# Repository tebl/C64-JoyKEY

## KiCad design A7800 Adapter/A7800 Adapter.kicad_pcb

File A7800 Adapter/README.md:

# JoyKEY (Atari 7800 Adapter)
**UNTESTED**

In the age of the Commmodore 64, Atari decided that it was a good idea to put together a console without audio quality that would only rise to the level of competing with the almighty ZX Spectrum. Then they launched them with horrible controllers that fell part on the way home from the store. Here in Europe, we also got treated to a gamepad-like controller that can only be described as an implement created by someone who only have had the concept just barely described to them over the phone - yet, we still got the feeling that they hated gamers.

Enough about all that, I actually have more than one of the consoles - somehow I sort of like playing on them, I just can't use any of their controllers. I've previously made an adapter so that I can use Sega Mega Drive controllers with the console, but since I've built the *C64 JoyKEY* I wanted to use it on that as well (which is the reason for this adapter).

# BOM
The parts listed are the ones I've used when building an Atari 7800 controller adapter for the *C64 JoyKEY*, part listed in parenthesis are considered optional (meaning you could build a more limited version of it). 

| Reference     | Item                                      | Count |
| ------------- | ----------------------------------------- | ----- |
| PCB           | Fabricate using Gerber files ([order]())  |    (1)|
| J1 *          | 2x5 pin straight header pins or 2x5 IDC   |     1 |
| J2 **         | DE-9 Female straight connector            |     1 |
| JP1,JP2 ***   | 3-pin breakable header pins (w/jumpers    |    (2)|

*) Breakable dual row pin headers can be used here, but I find it is nicer to use a 2x5 pin connector here instead. The cable needed is a 2x5 pin IDC cable (usually listed as *AVR* or *JTAG* cable) with sufficient length.

**) These are the blue kind with straight pins, it will include a few metal bits on it - remove those and you'll be left with the mostly blue part needed. Bend the pins slightly and match up with PCB, solder before it has a chance to fall off.

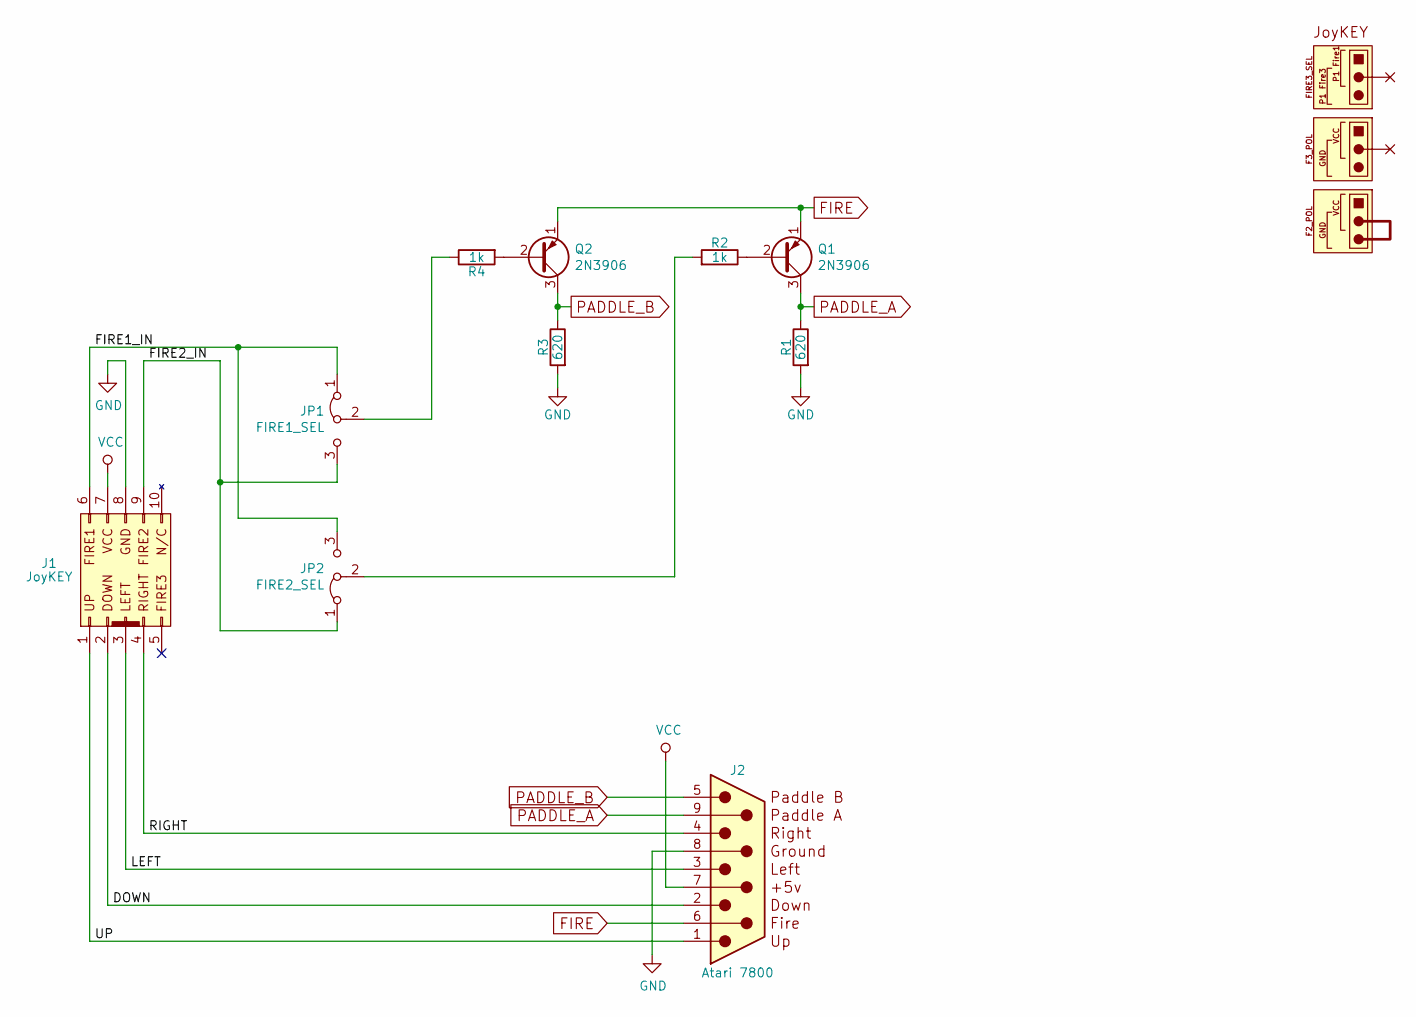
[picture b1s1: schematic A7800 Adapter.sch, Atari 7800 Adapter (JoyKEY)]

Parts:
J1: JoyKEY; IDC_Joystick
J2: Atari 7800; DSUB-9_Female_Edge
JP1: FIRE1_SEL; Pin_Header_Straight_1x03_Pitch2.54mm
JP2: FIRE2_SEL; Pin_Header_Straight_1x03_Pitch2.54mm
Q1, Q2: 2N3906; TO-92_Inline_Wide
R1, R3: 620; R_Axial_DIN0207_L6.3mm_D2.5mm_P10.16mm_Horizontal
R2, R4: 1k; R_Axial_DIN0207_L6.3mm_D2.5mm_P10.16mm_Horizontal

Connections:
/DOWN: J1.2, J2.2
/FIRE1_IN: J1.6, JP1.1 (A), JP2.3 (B)
/FIRE2_IN: J1.9, JP1.3 (B), JP2.1 (A)
/LEFT: J1.3, J2.3
/RIGHT: J1.4, J2.4
/UP: J1.1, J2.1
FIRE: J2.6, Q1.1 (E), Q2.1 (E)
GND: J1.8, J2.8 (GND), R1.2, R3.2
unnamed: JP1.2 (C), R4.1
unnamed: JP2.2 (C), R2.2
unnamed: Q1.2 (B), R2.1
unnamed: Q2.2 (B), R4.2
PADDLE_A: J2.9, Q1.3 (C), R1.1
PADDLE_B: J2.5, Q2.3 (C), R3.1
VCC: J1.7, J2.7 (VCC)

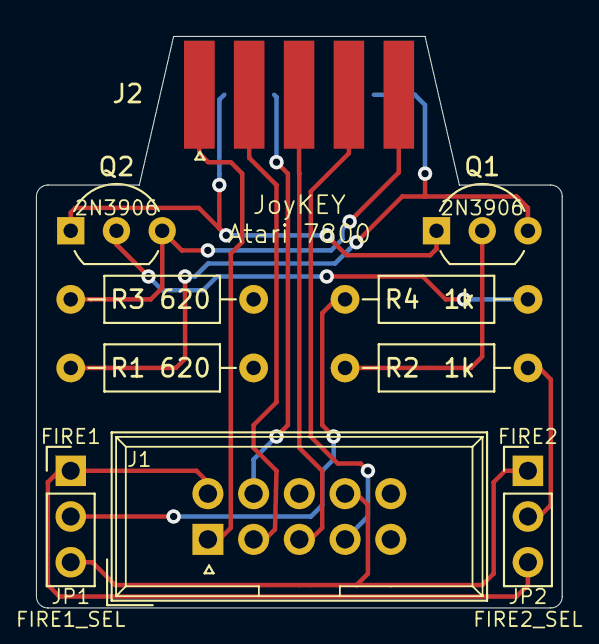
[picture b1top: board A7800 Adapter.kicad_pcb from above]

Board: 2 copper layers, 29.2 x 31.8 mm, 10 parts (0 on the bottom side), 15 nets.

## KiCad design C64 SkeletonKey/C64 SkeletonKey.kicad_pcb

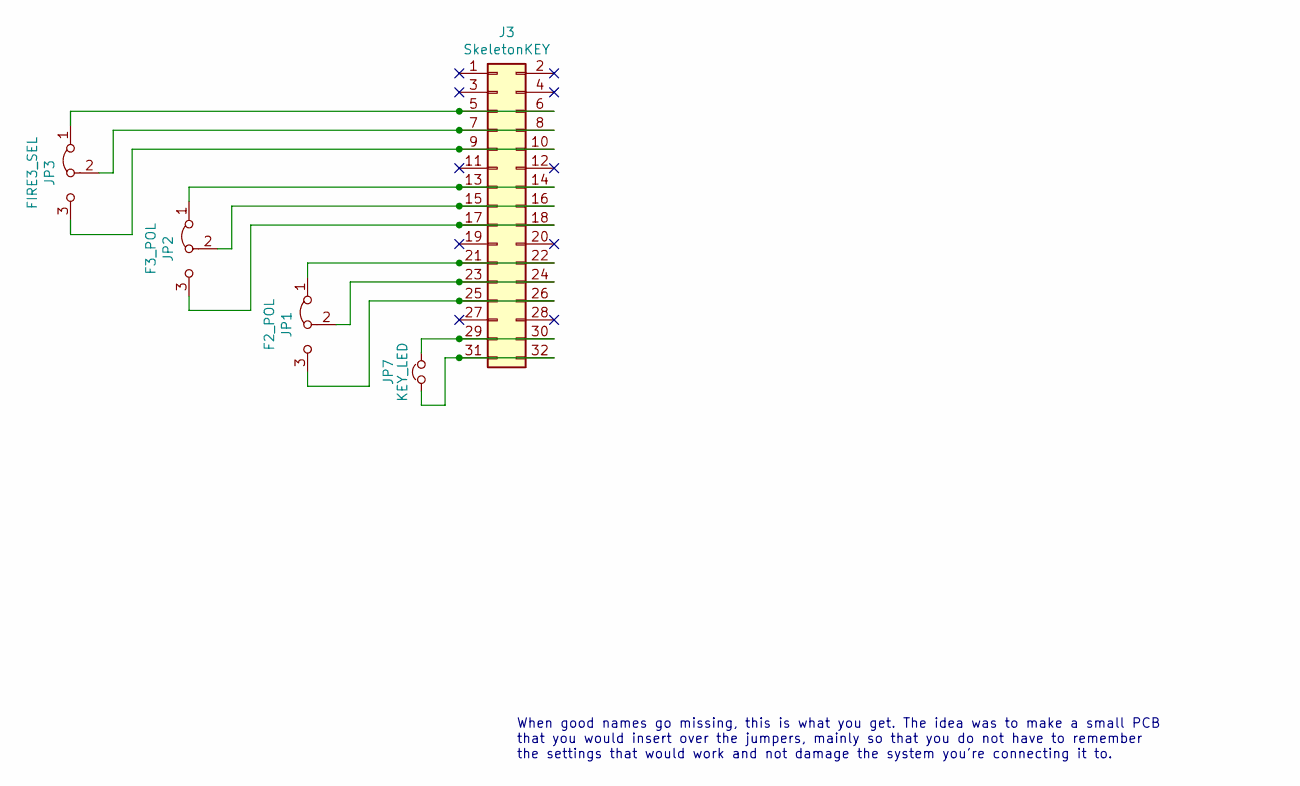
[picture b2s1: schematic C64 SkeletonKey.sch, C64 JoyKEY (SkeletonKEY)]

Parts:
J3: SkeletonKEY; PinHeader_2x16_P2.54mm_Vertical
JP1: F2_POL; select_r
JP2: F3_POL; select_r
JP3: FIRE3_SEL; select_r
JP7: KEY_LED; bridge_r

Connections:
unnamed: J3.5, J3.6, JP3.1 (A)
unnamed: J3.7, J3.8, JP3.2 (C)
unnamed: J3.9, J3.10, JP3.3 (B)
unnamed: J3.13, J3.14, JP2.1 (A)
unnamed: J3.15, J3.16, JP2.2 (C)
unnamed: J3.17, J3.18, JP2.3 (B)
unnamed: J3.21, J3.22, JP1.1 (A)
unnamed: J3.23, J3.24, JP1.2 (C)
unnamed: J3.25, J3.26, JP1.3 (B)
unnamed: J3.29, J3.30, JP7.1
unnamed: J3.31, J3.32, JP7.2

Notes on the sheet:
When good names go missing, this is what you get. The idea was to make a small PCB that you would insert over the jumpers, mainly so that you do not have to remember the settings that would work and not damage the system you're connecting it to.

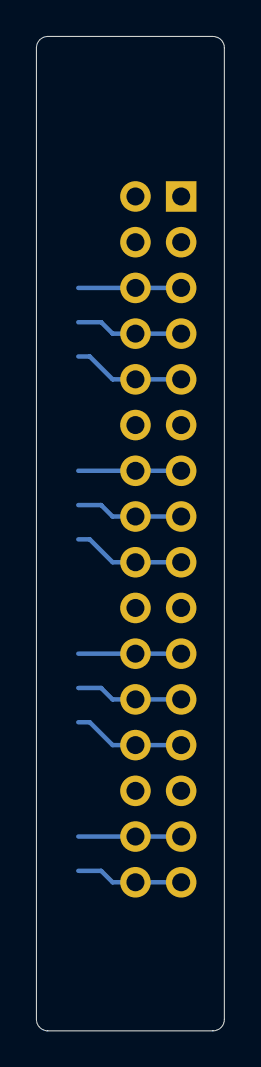
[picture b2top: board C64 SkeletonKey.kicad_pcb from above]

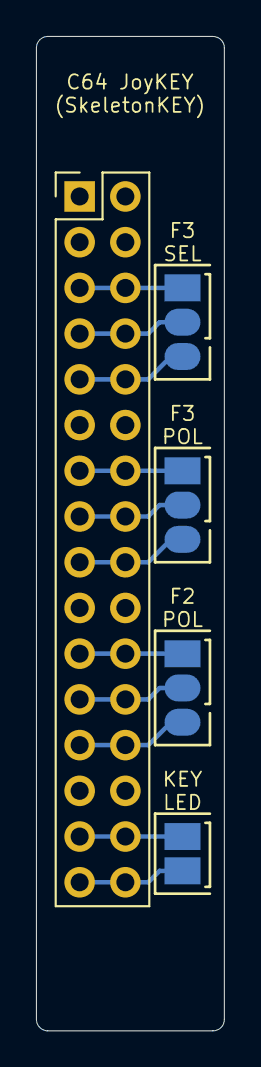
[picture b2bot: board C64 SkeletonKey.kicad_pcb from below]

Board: 2 copper layers, 10.4 x 55.2 mm, 5 parts (5 on the bottom side), 11 nets.

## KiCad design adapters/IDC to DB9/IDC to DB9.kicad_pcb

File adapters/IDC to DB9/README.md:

# IDC to DB9

An adapter that isn't actually an adapter might seem a bit strange at first look, but I promise that there's a use-case for it somewhere. One of them is that a few systems computers have recessed controller ports, the Commodore Amiga 600 is a rather common example of this. What that means in a slightly lesser amount of words, not by much, is that most DB9 connectors won't fit on these systems without using a hacksaw. That's why I created this small adapter, that is just a straight plug from 2x5 IDC to DB9. Another reason is that this way you can actually build the whole system without actually soldering wires onto a connector.

Given the rather generic use of this module compared to the others, I can't say anything about said systems ability to power a C64 JoyKEY with backlights and the whole package - I've added a power jumper so that we can stop the module from drawing power from the system (short **VCC_EN** if you know what you're doing).

# BOM
The parts listed are the ones I've used when building a Sinclair adapter for use with the *C64 JoyKEY*, part listed in parenthesis are considered optional (meaning you could build a more limited version of it). 

| Reference     | Item                                      | Count | Order   |
| ------------- | ----------------------------------------- | ----- | ------- |
| PCB           | Fabricate using Gerber files              |    (1)| [PCBway](https://www.pcbway.com/project/shareproject/C64_JoyKEY__IDC_to_DB9_.html)
| J1 *          | 2x5 pin straight header pins or 2x5 IDC   |     1 |
| J2 **         | DE-9 Female straight connector            |     1 |

*) Breakable dual row pin headers can be used here, but I find it is nicer to use a 2x5 pin connector here instead. The cable needed is a 2x5 pin IDC cable (usually listed as *AVR* or *JTAG* cable) with sufficient length.

**) These are the blue kind with straight pins, it will include a few metal bits on it - remove those and you'll be left with the mostly blue part needed. Bend the pins slightly and match up with PCB, solder before it has a chance to fall off.

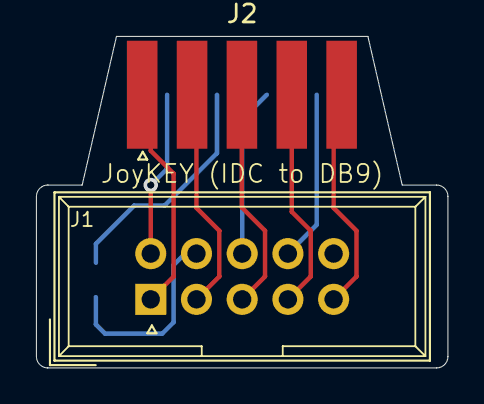
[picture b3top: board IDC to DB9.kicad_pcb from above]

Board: 2 copper layers, 22.9 x 18.4 mm, 3 parts (1 on the bottom side), 10 nets.

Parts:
J1: JoyKEY; IDC_Joystick
J2: DB9; DSUB-9_Female_Edge
JP1: PWR; bridge

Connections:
/DOWN: J1.2, J2.2
/FIRE1: J1.6, J2.6
/FIRE2: J1.9, J2.9
/FIRE3: J1.5, J2.5
/LEFT: J1.3, J2.3
/RIGHT: J1.4, J2.4
/UP: J1.1, J2.1
GND: J1.8, J2.8
unnamed: J1.7, JP1.1
VCC: J2.7, JP1.2

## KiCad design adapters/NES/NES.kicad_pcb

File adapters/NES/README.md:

# JoyKEY (Nintendo Entertainment System)
The Nintendo Entertainment System, commonly known as just the *NES* came with a four button controller (*B*, *A*, *SELECT* and *START*). A picture of the completed adapter has been included below, including the jumper position that you need to use on the *C64 JoyKEY* device itself.  For the later revisions of the *C64 JoyKEY* you'll have a row of buttons on the bottom left of the device, these are ideal for using as the  *SELECT* and *START* - for earlier revisions you'd install a physical *START*-button on the adapter itself.

Making the adapter requires a cable with the right shape, Nintendo wanted these to be explicitly proprietary so you can't exactly order one from electronic parts vendors though obtaining one isn't exactly hard. The simplest way of obtaining the plug today is either cutting up cheap NES controller extension cable, alternatively you could just purchase one of the rather horrible cloned controllers and cut it off from that instead. Both of these options should be readily available from your favourite off-brand marketplace for all things "*Made in China*", AliExpress, Ebay, Wish and most similar sites.

With the cut-off cable in hand, the individual strands of the cable can then be soldered to the adapter PCB. The pins are numbered left to right, match up the individual strands to the pin numbering as shown in the [schematic](https://github.com/tebl/C64-JoyKEY/blob/main/documentation/schematic/adapters/NES.pdf). Ideally I'd like to just tell you where to connect them based on the colour, but with the cost of these things I wouldn't expect them to be identical across all of them - so just use your multimeter in order to identify what goes where on the connector.

# BOM
The parts listed are the ones I've used when building a Nintendo Entertainment System controller adapter for the *C64 JoyKEY*, part listed in parenthesis are considered optional (meaning you could build a more limited version of it).

| Reference     | Item                                      | Count | Order  |
| ------------- | ----------------------------------------- | ----- | ------ |
| PCB           | Fabricate using Gerber files              |     1 | [PCBWay](https://www.pcbway.com/project/shareproject/C64_JoyKEY_NES_adapter_74ada4a5.html)
| J1,J2 *       | 2x5 pin straight header pins or 2x5 IDC   |     2 |
| J3            | Male end of NES extension cable           |     1 |
| JP1           | 2-pin breakable header pins (w/jumpers)   |    (1)|
| R1-R8         | 1k ohm resistor                           |     9 | 
| SW1 **        | 6x6mm momentary tactile switch            |    (1)|
| U1            | CD4021BE (DIP-16)                         |     1 |

*) Breakable dual row pin headers can be used here, but I find it is nicer to use a 2x5 pin connector here instead. The cable needed is a 2x5 pin IDC cable (usually listed as *AVR* or *JTAG* cable) with sufficient length, these are used with all adapters.

**) This switch is only required using an earlier revision of the *C64 JoyKEY*, the three extra switches were added in revision E.

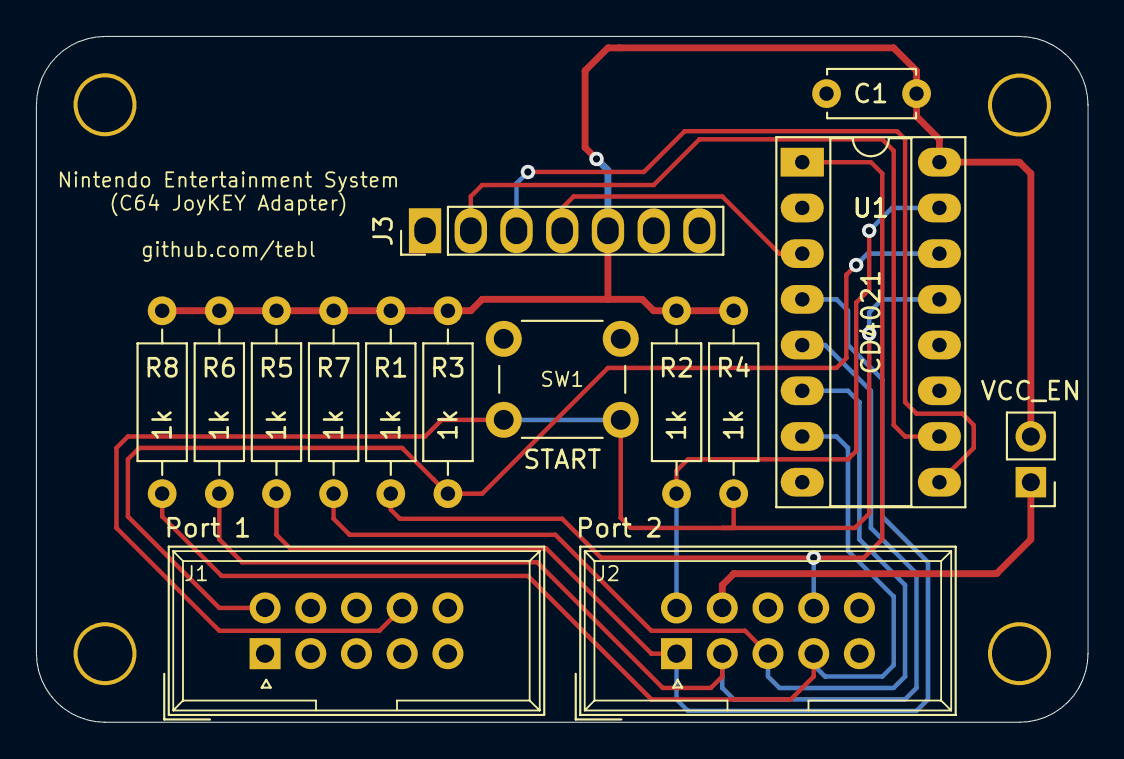
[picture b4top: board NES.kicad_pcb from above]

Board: 2 copper layers, 58.4 x 38.1 mm, 19 parts (0 on the bottom side), 14 nets.

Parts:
C1: 100nF; C_Disc_D4.7mm_W2.5mm_P5.00mm
J1: Port 1; IDC_Joystick
J2: Port 2; IDC_Joystick
J3: NES_Gamepad; NES_Output
JP1: VCC_EN; PinHeader_1x02_P2.54mm_Vertical
M1, M2, M3, M4: Mounting; M3_pin
R1, R2, R3, R4, R5, R6, R7, R8: 1k; R_Axial_DIN0207_L6.3mm_D2.5mm_P10.16mm_Horizontal
SW1: START; SW_PUSH_6mm
U1: CD4021; DIP-16_W7.62mm_Socket_LongPads

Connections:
/A: J2.9, R1.2, U1.1
/B: J2.6, R2.2, U1.15
/DOWN: J2.2, R6.2, U1.5
/LEFT: J2.3, R7.2, U1.6
/RIGHT: J2.4, R8.2, U1.7
/SELECT: J1.6, R3.2, U1.14
/START: J1.9, R4.2, SW1.2, U1.13
/UP: J2.1, R5.2, U1.4
CLK: J3.2, U1.10
DATA: J3.4, U1.3
GND: C1.2, J1.8, J2.8, J3.1, SW1.1, U1.8, U1.11
LATCH: J3.3, U1.9
unnamed: J2.7, JP1.1
VCC: C1.1, J3.5, JP1.2, R1.1, R2.1, R3.1, R4.1, R5.1, R6.1, R7.1, R8.1, U1.16

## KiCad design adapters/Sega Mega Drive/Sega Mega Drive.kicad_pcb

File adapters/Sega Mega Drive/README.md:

# JoyKEY (Sega Mega Drive)

The Sega Mega Drive, released as the Sega Genesis in North America, originally came with a what is now known as the 3-button controller though it actually had the *START* button as a fourth button as well. While it was designed to be backwards compatible with the Sega Master System, it had a few tricks up its sleeve by adding a digital multiplexer chip that would read out the buttons over a few wires instead of having dedicated wires for each button (like previous Atari-style pinouts). There was also a 6-button controller released later, but for now I've chosen to instead focus on the 3-button controller instead - simply because we only have 3 buttons on the *C64 JoyKEY* (the *START* button has been placed on the actual adapter instead).

The completed adapter can be seen below, this also includes the jumpers that should be set on the *C64 JoyKEY* device itself. Note that because of the recessed controller ports on the actual console, a larger connector such as the DB9 IDC variety will not fit into the console - I've solved that by using a straight [IDC to DB9](https://github.com/tebl/C64-JoyKEY/tree/main/adapters/IDC%20to%20DB9) adapter as well.

# BOM
The parts listed are the ones I've used when building a Sega Mega Drive controller adapter for the *C64 JoyKEY*, part listed in parenthesis are considered optional (meaning you could build a more limited version of it). Additionally, check out the BOM on the [IDC to DB9](https://github.com/tebl/C64-JoyKEY/tree/main/adapters/IDC%20to%20DB9) page - if you don't already have on of these ready to go.

| Reference     | Item                                      | Count | Order  |
| ------------- | ----------------------------------------- | ----- | ------ |
| PCB           | Fabricate using Gerber files              |    (1)| [PCBway](https://www.pcbway.com/project/shareproject/C64_JoyKEY__Sega_Mega_Drive_Genesis_adapter_.html)
| C1            | 100nF ceramic capacitor (5mm)             |     1 |
| J1 *          | 2x5 pin straight header pins or 2x5 IDC   |    (1)|
| J2,J3 *       | 2x5 pin straight header pins or 2x5 IDC   |     2 |
| J4            | 3-pin dual row breakable pin headers      |    (1)|
| JP1           | 2-pin breakable header pins (w/jumpers)   |    (1)|
| R1-R9         | 10k ohm resistor                          |     9 | 
| SW1           | 6x6mm momentary tactile switch            |     1 |

*) Breakable dual row pin headers can be used here, but I find it is nicer to use a 2x5 pin connector here instead. The cable needed is a 2x5 pin IDC cable (usually listed as *AVR* or *JTAG* cable) with sufficient length.

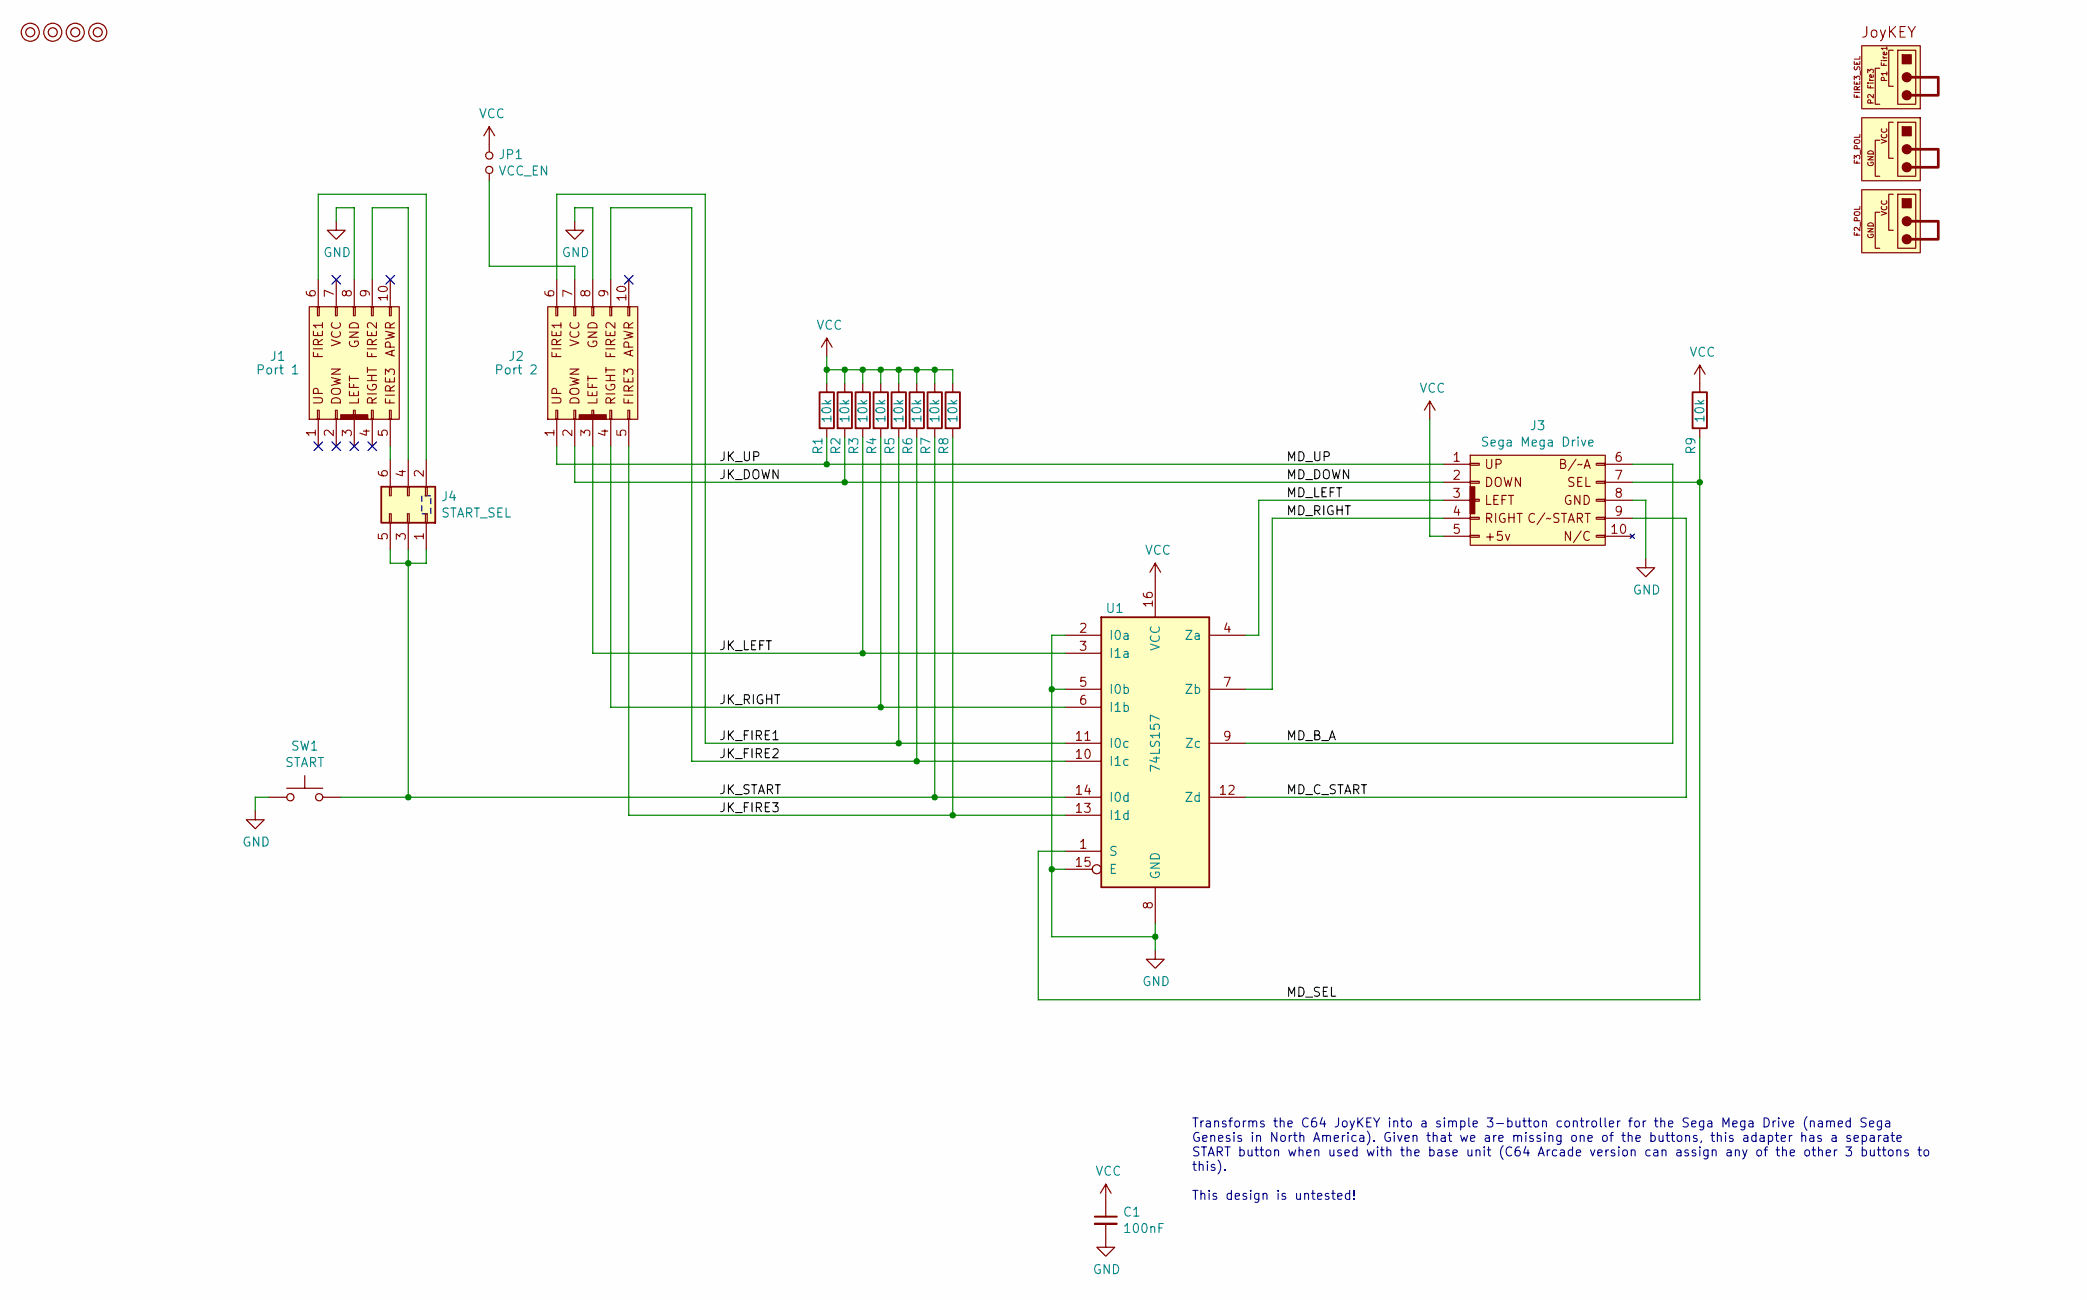
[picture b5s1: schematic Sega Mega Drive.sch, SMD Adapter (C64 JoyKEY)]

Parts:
C1: 100nF; C_Disc_D4.7mm_W2.5mm_P5.00mm
J1: Port 1; IDC_Joystick
J2: Port 2; IDC_Joystick
J3: Sega Mega Drive; IDC_Joystick
J4: START_SEL; PinHeader_2x03_P2.54mm_Vertical
JP1: VCC_EN; PinHeader_1x02_P2.54mm_Vertical
M1, M2, M3, M4: Mounting; M3_pin
R1, R2, R3, R4, R5, R6, R7, R8, R9: 10k; R_Axial_DIN0207_L6.3mm_D2.5mm_P10.16mm_Horizontal
SW1: START; SW_PUSH_6mm
U1: 74LS157; DIP-16_W7.62mm_Socket_LongPads

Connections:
/JK_DOWN: J2.2, J3.2, R2.2
/JK_FIRE1: J2.6, R5.2, U1.11 (I0c)
/JK_FIRE2: J2.9, R6.2, U1.10 (I1c)
/JK_FIRE3: J2.5, R8.2, U1.13 (I1d)
/JK_LEFT: J2.3, R3.2, U1.3 (I1a)
/JK_RIGHT: J2.4, R4.2, U1.6 (I1b)
/JK_START: J4.1, J4.3, J4.5, R7.2, SW1.2, U1.14 (I0d)
/JK_UP: J2.1, J3.1, R1.2
/MD_B_A: J3.6, U1.9 (Zc)
/MD_C_START: J3.9, U1.12 (Zd)
/MD_LEFT: J3.3, U1.4 (Za)
/MD_RIGHT: J3.4, U1.7 (Zb)
/MD_SEL: J3.7, R9.2, U1.1 (S)
GND: C1.2, J1.8, J2.8, J3.8, SW1.1, U1.2 (I0a), U1.5 (I0b), U1.8 (GND), U1.15 (E)
unnamed: J1.5, J4.6
unnamed: J1.6, J4.2
unnamed: J1.9, J4.4
unnamed: J2.7, JP1.2
VCC: C1.1, J3.5, JP1.1, R1.1, R2.1, R3.1, R4.1, R5.1, R6.1, R7.1, R8.1, R9.1, U1.16 (VCC)

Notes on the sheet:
Transforms the C64 JoyKEY into a simple 3-button controller for the Sega Mega Drive (named Sega Genesis in North America). Given that we are missing one of the buttons, this adapter has a separate START button when used with the base unit (C64 Arcade version can assign any of the other 3 buttons to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

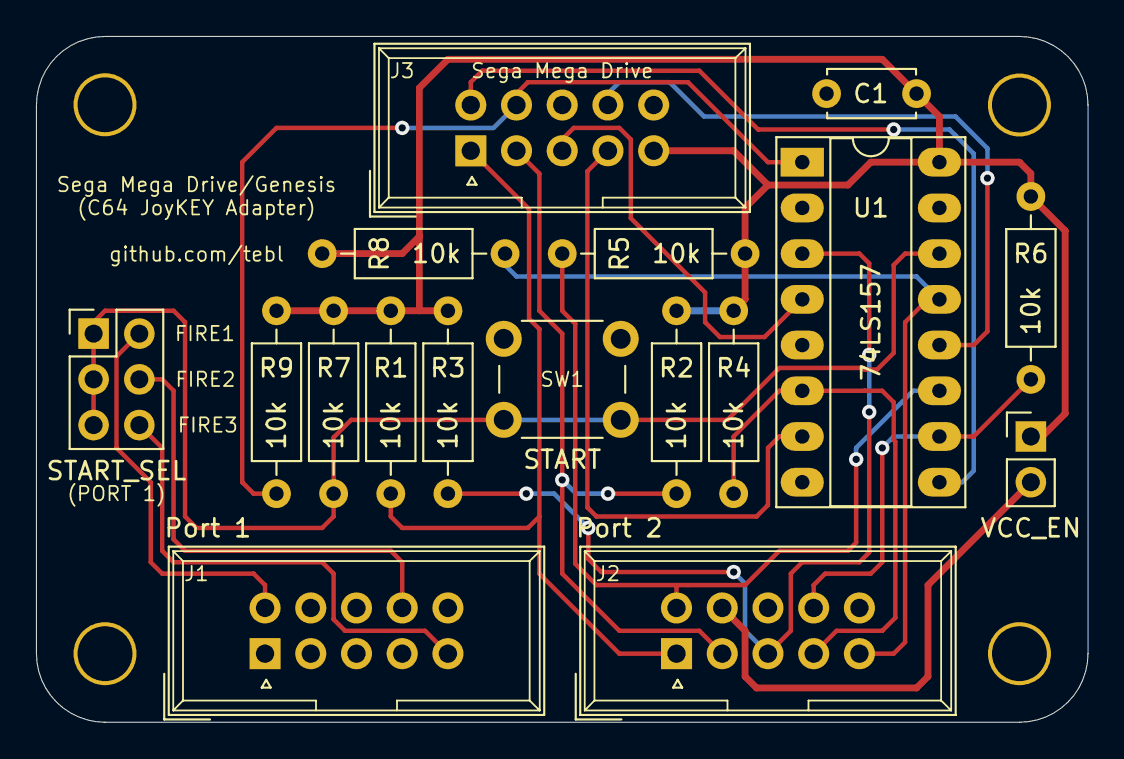
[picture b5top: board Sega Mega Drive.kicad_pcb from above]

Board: 2 copper layers, 58.4 x 38.1 mm, 21 parts (0 on the bottom side), 19 nets.

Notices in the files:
adapters/NES/NES.kicad_pcb:
Licensed under
CERN OHL v1.2
